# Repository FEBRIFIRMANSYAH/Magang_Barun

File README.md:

# Electric Remote-Controlled Boat System

## Deskripsi
Sistem ini adalah perancangan kapal yang dikendalikan menggunakan remote control dengan sumber tenaga listrik. Sistem ini memanfaatkan beberapa komponen utama untuk mengontrol pergerakan kapal dan memastikan kelancaran operasinya.

---

## Diagram Sistem
Sistem terdiri dari **9 komponen utama** yang saling terhubung untuk menjalankan fungsi penggerak dan kontrol kapal secara optimal.

---

## Komponen Utama

### 1. Battery
- Sumber daya listrik utama untuk seluruh sistem.  
- Memberikan daya ke **Boost/Buck Converter** untuk menyesuaikan kebutuhan tegangan komponen lainnya.

### 2. Boost/Buck Converter
- Mengatur tegangan dari baterai agar stabil dan sesuai dengan kebutuhan masing-masing komponen, seperti ESC dan Receiver.

### 3. ESC (Electronic Speed Controller)
- Mengontrol kecepatan dan arah motor BLDC berdasarkan sinyal dari Receiver.  
- Berfungsi sebagai penghubung antara motor BLDC dan sistem kontrol.

### 4. BLDC Motor
- Mengubah energi listrik menjadi energi mekanik untuk menggerakkan **Propeller**.

### 5. Propeller
- Menghasilkan gaya dorong untuk menggerakkan kapal maju atau mundur di air.  
- Diputar oleh **BLDC Motor**.

### 6. Receiver
- Menerima sinyal kontrol dari **Remote/Transmitter** dan meneruskannya ke **ESC** dan **Servo**.  
- Menjadi penghubung antara pengguna dan komponen kapal.

### 7. Remote/Transmitter
- Perangkat pengendali jarak jauh yang mengirimkan perintah ke **Receiver** untuk mengatur kecepatan dan arah kapal.

### 8. Servo
- Mengontrol posisi **Rudder** berdasarkan sinyal dari **Receiver**.  
- Memungkinkan kapal untuk berbelok ke kiri atau kanan.

### 9. Rudder
- Berfungsi sebagai kemudi untuk mengatur arah kapal.  
- Posisi **Rudder** dikontrol oleh **Servo**.

---

## Alur Kerja Sistem

### 1. Penyediaan Daya
- **Battery** menyediakan daya ke seluruh sistem.
- Tegangan distabilkan oleh **Boost/Buck Converter** untuk digunakan oleh komponen seperti **ESC** dan **Receiver**.

### 2. Pengendalian Jarak Jauh
- Pengguna menggunakan **Remote/Transmitter** untuk mengirimkan sinyal kontrol ke **Receiver**.

### 3. Distribusi Sinyal
- **Receiver** mendistribusikan sinyal ke:  
  - **ESC**, untuk mengatur kecepatan dan arah putaran **BLDC Motor**.  
  - **Servo**, untuk mengontrol posisi **Rudder**.

### 4. Pergerakan Kapal
- **ESC** mengatur putaran **BLDC Motor**, yang memutar **Propeller** untuk menggerakkan kapal.
- **Servo** mengatur orientasi **Rudder**, menentukan arah kapal.

### 5. Navigasi Kapal
- Kapal bergerak sesuai kombinasi kontrol pada **Propeller** dan **Rudder**, berdasarkan perintah dari **Remote/Transmitter**.

---

## Daftar Pustaka
Raharja, L. P. S., Darmawan, A., Kristio, P., & Nugroho, P. (2023). Rancang Bangun Prototipe Kapal Elektrik Dengan Sistem Kendali Jarak Jauh. *Jurnal Teknologi Terpadu, 11*(1), 1-xx. ISSN: 2338-6649.

# Remote-Controlled Fuel Engine Boat System

## Deskripsi
Sistem ini adalah perancangan dan implementasi dari kapal berbahan bakar mesin yang dikendalikan secara jarak jauh menggunakan remote control. Kapal ini dilengkapi dengan berbagai komponen elektronik dan mekanik yang bekerja secara bersama-sama untuk memastikan kontrol yang baik.

---

## Diagram Sistem
Sistem ini terdiri dari **11 komponen utama**, yang masing-masing memiliki fungsi spesifik dalam mendukung operasi kapal.

---

## Komponen Utama

1. **Battery**
   - Menyediakan daya listrik untuk semua komponen elektronik, seperti receiver, servo, motor, dan lainnya.
   - Tegangan dari baterai dikendalikan agar sesuai kebutuhan dengan bantuan Boost/Buck Converter.

2. **Boost/Buck Converter**
   - Mengatur tegangan dari baterai agar stabil sesuai dengan kebutuhan masing-masing komponen elektronik, seperti Receiver dan Motor.

3. **Remote/Transmitter**
   - Mengirimkan sinyal kontrol dari pengguna ke kapal.
   - Sinyal ini mencakup perintah untuk mengatur gas mesin (**Linear Actuator**) dan arah kapal (**Servo**).

4. **Receiver**
   - Menerima sinyal dari **Remote/Transmitter**.
   - Mendistribusikan perintah ke:
     - **Servo**, untuk mengontrol **Rudder** (kemudi kapal).
     - **Linear Actuator**, untuk mengontrol gas pada mesin.

5. **Gas Tank**
   - Menyimpan bahan bakar yang disuplai ke **Fuel Engine**.
   - Memastikan mesin dapat bekerja terus-menerus selama bahan bakar tersedia.

6. **Propeller**
   - Mengubah tenaga mekanis dari **Fuel Engine** menjadi gaya dorong untuk menggerakkan kapal di atas air.

7. **Rudder**
   - Berfungsi sebagai kemudi untuk mengarahkan kapal.
   - Orientasi **Rudder** dikontrol oleh **Servo**, memungkinkan kapal berbelok ke kiri atau kanan.

8. **Servo**
   - Mengontrol posisi **Rudder**, yang menentukan arah kapal sesuai perintah dari remote control.

9.  **Linear Actuator**
    - Mengontrol gas pada kapal.

10. **Water Pump**
    - Berfungsi untuk memompa air, yang biasanya digunakan untuk sistem pendinginan mesin atau aplikasi lainnya.
    - Digunakan bersama **Motor**, yang menggerakkan pompa untuk menjaga aliran air yang stabil.

---

## Alur Kerja Sistem

1. **Battery** menyediakan daya ke seluruh sistem. Tegangan dari baterai distabilkan dengan **Boost/Buck Converter** sebelum dialirkan ke komponen lainnya.

2. Pengguna menggunakan **Remote/Transmitter** untuk mengirimkan sinyal kontrol ke **Receiver**.

3. **Receiver** menerima sinyal kontrol dari remote dan meneruskannya ke:
   - **Servo**, untuk mengontrol arah kapal melalui **Rudder**.
   - **Linear Actuator**, untuk mengatur gas pada supaya bisa berjalan.

4. **Propeller** menghasilkan gaya dorong yang memungkinkan kapal bergerak di atas air.

5. Arah kapal dikendalikan oleh **Rudder**, yang posisinya diatur oleh **Servo**, sesuai perintah dari remote.

6. Maju kapal diatur melalui **Linear Actuator**, yang mengontrol gas pada kapal.

7. **Water Pump**, digerakkan oleh **Motor**, memompa air yang dapat digunakan untuk sistem pendinginan mesin atau aplikasi lainnya.

---

## Daftar Pustaka

- Adwinda, E. G. (2024). RC Boat Fuel Engine. Tidak diterbitkan.

---

# Magang Implementasi bahasa C

         #include <stdio.h>
         #include <stdint.h>

         // =======================
         // Kasus 1: Penjumlahan Variabel
         // =======================
         void kasus1() {
            int a = 1, b = 2;
            int calculate;

            // Operasi penjumlahan
            calculate = a + b; // a=1, b=2, calculate = 3
            printf("Kasus 1: Hasil penjumlahan a dan b adalah: %d\n", calculate);

            // Modifikasi nilai a
            a = a + 1; // a sekarang bernilai 2
            printf("Kasus 1: Nilai a setelah ditambah 1 adalah: %d\n\n", a);
         }

         // =======================
         // Kasus 2: Input dan Output Variabel
         // =======================
         void kasus2() {
            int integer1;
            printf("Kasus 2: Masukkan sebuah bilangan bulat: ");
            scanf("%d", &integer1); // Mengambil input dan menyimpannya ke integer1
            printf("Kasus 2: Bilangan yang Anda masukkan adalah: %d\n\n", integer1);
         }

         // =======================
         // Kasus 3: Ukuran Memori dan Tipe Data
         // =======================
         void kasus3() {
            uint8_t eightBitVariable = 250; // Memakai 8-bit memori
            unsigned int unsignedInt = 255; // Standar 32-bit untuk unsigned int
            printf("Kasus 3: eightBitVariable: %d, ukuran memori: %lu bytes\n", eightBitVariable, sizeof(eightBitVariable));
            printf("Kasus 3: unsignedInt: %u, ukuran memori: %lu bytes\n\n", unsignedInt, sizeof(unsignedInt));
         }

         // =======================
         // Kasus 4: Operasi Float dan Pembagian
         // =======================
         void kasus4() {
            float floatValue1 = 20.0f;
            float floatValue2 = 30.0f;
            float dividedValue = floatValue1 / floatValue2; // 20 / 30 = 0.666...
            printf("Kasus 4: Hasil pembagian %.2f / %.2f adalah: %.2f\n\n", floatValue1, floatValue2, dividedValue);
         }

         // =======================
         // Kasus 5: Manipulasi String dan Karakter
         // =======================
         void kasus5() {
            char stringArray[][6] = {"Arund", "Taib", "Anton"}; // Array string dengan elemen tetap
            printf("Kasus 5: Nama ketiga pada array string adalah: %s\n", stringArray[2]);

            // Menampilkan setiap karakter dalam string
            printf("Kasus 5: Karakter-karakter dalam nama ketiga:\n");
            for (int i = 0; stringArray[2][i] != '\0'; i++) { // Iterasi hingga null terminator
               printf("%c ", stringArray[2][i]);
            }
            printf("\n\n");
         }

         // =======================
         // Kasus 6: Operasi Aritmatika
         // =======================
         void kasus6() {
            int a = 5, b = 2;
            printf("Kasus 6: Operasi Aritmatika\n");
            printf("%d + %d = %d\n", a, b, a + b);
            printf("%d - %d = %d\n", a, b, a - b);
            printf("%d * %d = %d\n", a, b, a * b);
            printf("%d / %d = %d\n", a, b, a / b);
            printf("%d %% %d = %d\n\n", a, b, a % b);
         }

         // =======================
         // Kasus 7: Operasi Bitwise
         // =======================
         void kasus7() {
            unsigned int a = 5, b = 9;
            printf("Kasus 7: Operasi Bitwise\n");
            printf("a & b = %u\n", a & b);
            printf("a | b = %u\n", a | b);
            printf("a ^ b = %u\n", a ^ b);
            printf("~a = %u\n", ~a);
            printf("b << 1 = %u\n", b << 1);
            printf("b >> 1 = %u\n\n", b >> 1);
         }

         // =======================
         // Kasus 8: Percabangan
         // =======================
         void kasus8() {
            int nilai;
            printf("Kasus 8: Percabangan\n");
            printf("Masukkan nilai ujian: ");
            scanf("%d", &nilai);

            if (nilai >= 80) {
               printf("Nilai : A\n");
            } else if (nilai >= 70) {
               printf("Nilai : B\n");
            } else if (nilai >= 60) {
               printf("Nilai : C\n");
            } else {
               printf("Nilai : D\n");
            }
            printf("\n");
         }

         // =======================
         // Kasus 9: Perulangan dan Sorting
         // =======================
         void kasus9() {
            int arr[5] = {10, 2, 5, 11, 3};
            int tmp;

            printf("Kasus 9: Perulangan dan Sorting (Bubble Sort)\n");
            printf("Array sebelum sorting: ");
            for (int i = 0; i < 5; i++) {
               printf("%d ", arr[i]);
            }
            printf("\n");

            for (int i = 0; i < 5 - 1; i++) {
               for (int j = 0; j < 5 - i - 1; j++) {
                     if (arr[j] > arr[j + 1]) {
                        tmp = arr[j + 1];
                        arr[j + 1] = arr[j];
                        arr[j] = tmp;
                     }
               }
            }

            printf("Array setelah sorting: ");
            for (int i = 0; i < 5; i++) {
               printf("%d ", arr[i]);
            }
            printf("\n\n");
         }

         // =======================
         // Kasus 10: Switch Case
         // =======================
         void kasus10() {
            int hari;
            printf("Kasus 10: Switch Case\n");
            printf("Masukkan angka (1-7) untuk memilih hari: ");
            scanf("%d", &hari);

            switch (hari) {
               case 1:
                     printf("Hari Senin\n");
                     break;
               case 2:
                     printf("Hari Selasa\n");
                     break;
               case 3:
                     printf("Hari Rabu\n");
                     break;
               case 4:
                     printf("Hari Kamis\n");
                     break;
               case 5:
                     printf("Hari Jumat\n");
                     break;
               case 6:
                     printf("Hari Sabtu\n");
                     break;
               case 7:
                     printf("Hari Minggu\n");
                     break;
               default:
                     printf("Hari tidak valid\n");
                     break;
            }
            printf("\n");
         }

         int main() {
            // Menjalankan semua kasus secara berurutan
            kasus1();
            kasus2();
            kasus3();
            kasus4();
            kasus5();
            kasus6();
            kasus7();
            kasus8();
            kasus9();
            kasus10();

            return 0;
         }
         // End of program

# Magang Electrical Design
## Schematics Design

Boost Converter:
### Cara kerja
- Rangkaian ini menaikkan tegangan dari 5V menjadi 12V.
- Komponen utama yang bekerja di sini adalah IC LM2577, induktor, dioda, resistor, dan kapasitor.
- Induktor menyimpan energi, dioda mengalirkan arus ke output, dan kapasitor menjaga tegangan agar stabil.
  
### Bagian Utama Rangkaian:

- Input (J2): Masukan tegangan 5V.
- Induktor (L1): Komponen ini menyimpan dan melepaskan energi untuk menaikkan tegangan.
- IC LM2577: Mengontrol proses menaikkan tegangan dengan mengatur switching.
- Dioda (D1): Mengarahkan arus dari induktor ke kapasitor dan beban.
- Kapasitor Output (C3): Menjaga tegangan output tetap stabil.
- Resistor (R1 & R3): Mengatur nilai tegangan output melalui pin feedback (FB) di IC.

- Output (J1): Tegangan yang dihasilkan adalah 12V, yang bisa digunakan untuk memberi daya ke perangkat lain.
  
### Daftar Komponen:
- IC LM2577 - Mengatur proses boost (menaikkan tegangan).
- Induktor L1 (100 µH) - Menyimpan energi.
- Dioda D1 (1N5821) - Mengalirkan arus ke output dengan efisiensi tinggi.
Resistor:
- R1 (17.4 kΩ) dan R3 (2 kΩ) - Untuk mengatur tegangan output.
- R4 (2.2 kΩ) - Untuk pengaturan internal IC.
Kapasitor:
- C1 (0.1 µF) - Menstabilkan masukan.
- C2 (0.33 µF) - Membantu kestabilan rangkaian.
- C3 (680 µF) - Menstabilkan tegangan output.
- Konektor J1 dan J2 - Untuk menghubungkan input dan output.

## PCB Layout

###  PCB tersebut menggunakan 2 layer
## 3D Print Out

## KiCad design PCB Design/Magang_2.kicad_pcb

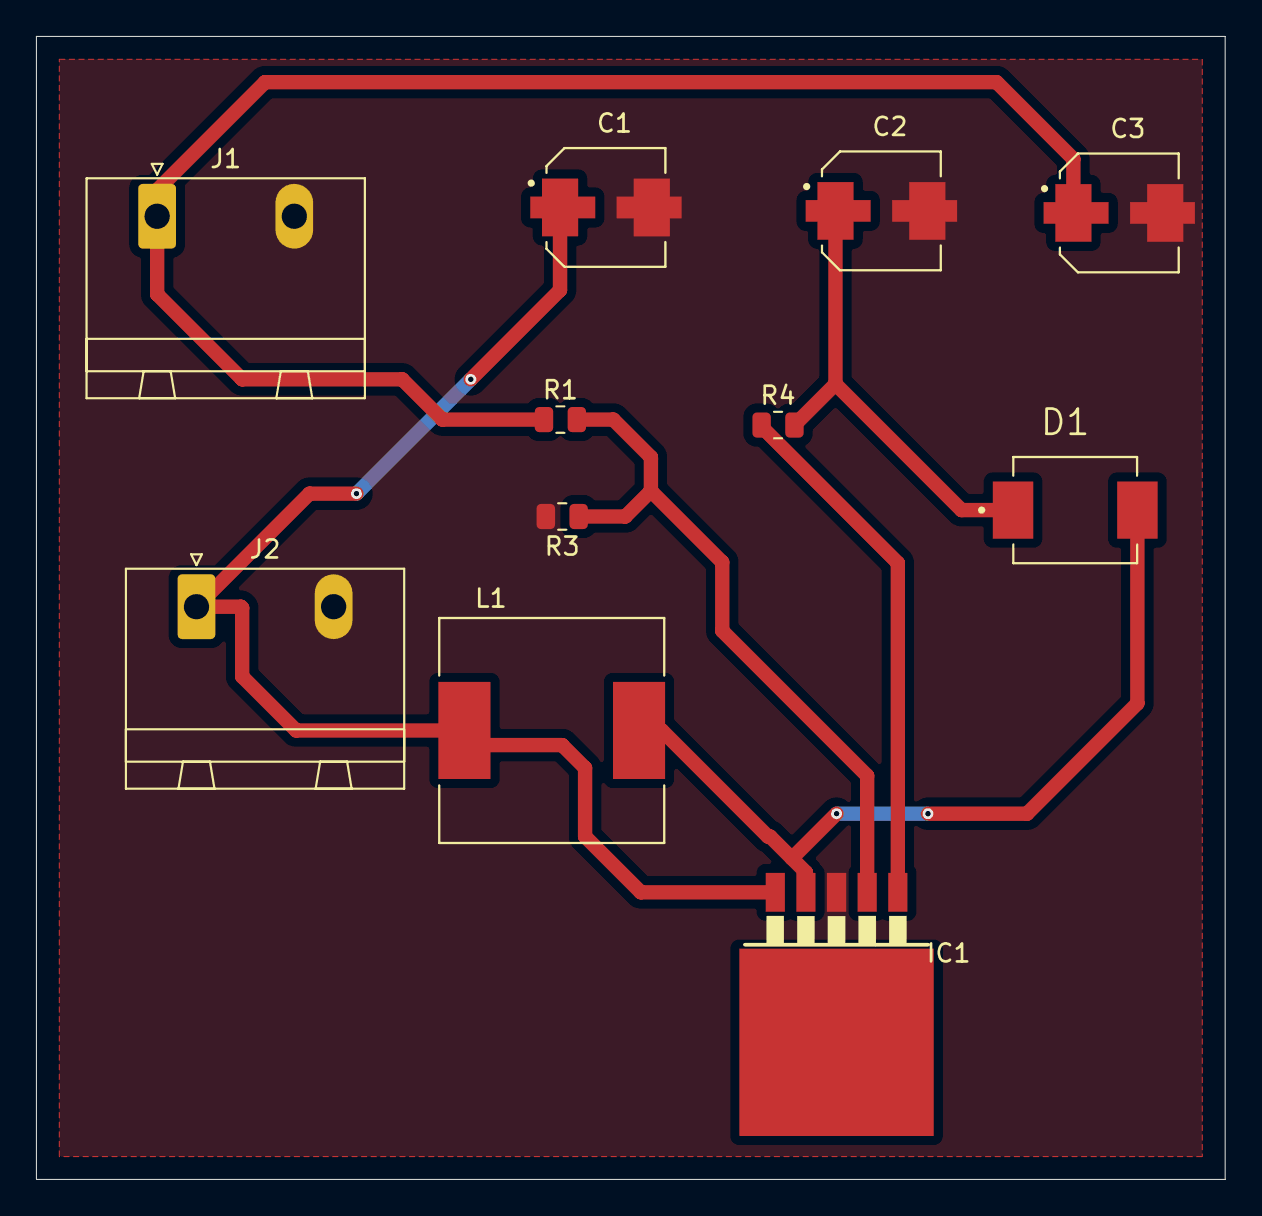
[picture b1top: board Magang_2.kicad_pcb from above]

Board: 2 copper layers, 66.0 x 63.5 mm, 11 parts (0 on the bottom side), 7 nets.

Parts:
C1: 0.1 uF; CAP_EEEFK1C101V
C2: 0.33 uF; CAP_EEEFK1C101V
C3: 680 uF; CAP_EEEFK1C101V
D1: 1N5821; DIOM7959X265N
IC1: LM2577; TO263-5
J1, J2: Conn_01x02_Socket; PhoenixContact_GMSTBA_2,5_2-G-7,62_1x02_P7.62mm_Horizontal
L1: 100 uH; INDP125125X600N
R1: 17.4k; R_0805_2012Metric
R3: 2k; R_0805_2012Metric
R4: 2.2k; R_0805_2012Metric

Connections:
+5V: C1.1, IC1.5 (VIN), J2.1, L1.1
+12V: C3.1, J1.1, R1.1
GND: C1.2, C2.2, C3.2, IC1.3 (GND), J1.2, J2.2, R3.2
unnamed: C2.1, D1.C, R4.2
unnamed: D1.e, IC1.4 (VSW), L1.2
unnamed: IC1.1 (COMP), R4.1
unnamed: IC1.2 (FB), R1.2, R3.1

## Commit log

2024-11-29 Main Repo
2024-11-29 Revisi PCB
